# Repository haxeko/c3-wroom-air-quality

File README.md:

# C3-WROOM Air Quality

Thiết bị đo chất lượng không khí dùng **ESP32-C3-WROOM-02**: bụi mịn PM1.0/PM2.5/PM10 (Plantower **PMS5003**), CO2/nhiệt độ/độ ẩm (Sensirion **SCD40**), màn hình **OLED 1.3" SH1106** và 3 LED RGB địa chỉ hóa báo trạng thái.

Repo gồm **phần cứng** (KiCad, file sản xuất JLCPCB) và **firmware** (Matter over Wi-Fi: Apple Home, Google Home, Home Assistant).

## Cấu trúc thư mục

```
.
├── hardware/                 Thiết kế phần cứng
│   ├── kicad/
│   │   ├── main/             Bản chính: 3 LED XL-1615, JLC lắp 2 mặt
│   │   ├── led2020/          Bản thử nghiệm: JLC lắp 1 mặt, tự hàn 3 LED WS2812B-2020
│   │   └── lib/              Thư viện ký hiệu + footprint dùng chung (PM25)
│   ├── production/<bản>/     File đặt JLCPCB: gerber, BOM, CPL
│   ├── docs/<bản>/           Sơ đồ nguyên lý PDF, layout PDF, BOM đầy đủ, tọa độ đầy đủ
│   ├── mechanical/           Đường viền board (DXF) để thiết kế vỏ
│   └── cost/                 Kho giá linh kiện + BOQ giá thành 1 sản phẩm
├── firmware/                 Firmware ESP32-C3: Matter over Wi-Fi (ESP-IDF + esp-matter)
│   ├── main/                 Mã nguồn; chân GPIO đặt trong main/Kconfig.projbuild (menuconfig)
│   └── docs/                 Kịch bản kiểm tra khi ghép nối thất bại
└── docs/                     Tài liệu: gán chân, đặt hàng JLC, hàn LED, sửa lỗi, lịch sử
```

## Thông số board

| Mục | Giá trị |
|---|---|
| Kích thước | 51,4 × 31,4 mm, 2 lớp, dày 1,6 mm, bo góc R1,7 |
| Anten | Khoét 6 × 19 mm ở cạnh phải, không đổ đồng vùng anten |
| Nguồn | USB-C chỉ cấp nguồn (5 V), cổng lồi khỏi mép board 1,2 mm |
| Ổn áp | AMS1117-3.3 cho ESP32 + OLED; AP2112K-3.3 riêng cho SCD40 |
| Nạp firmware | 6 pad tròn J5 (UART0 + IO9), xem [docs/pinout.md](docs/pinout.md) |
| Nút | SW2 TS-1187A nối IO10 (nút người dùng) |

## Các bản phần cứng

| Bản | Thư mục | Khác biệt |
|---|---|---|
| **main** (v25) | `hardware/kicad/main` | 3 LED XL-1615 (1,6 × 1,5 mm) do JLC hàn; linh kiện ở cả 2 mặt |
| **led2020** | `hardware/kicad/led2020` | JLC chỉ lắp mặt dưới; mặt trên tự hàn 3 LED WS2812B-2020; tụ LED và R7 chuyển xuống mặt dưới |

Bản cũ v19 (5 LED, header nạp xuyên lỗ, nút RESET ở EN) không có trong repo; xem [docs/changelog.md](docs/changelog.md).

## Bắt đầu nhanh

- **Mở thiết kế:** KiCad 7 trở lên, mở `hardware/kicad/main/pm25.kicad_pro`.
- **Đặt hàng:** làm theo [docs/assembly-jlcpcb.md](docs/assembly-jlcpcb.md).
- **Build và nạp firmware:** đọc [firmware/README.md](firmware/README.md). Chân GPIO đặt trong `idf.py menuconfig`; kiểm tra lỗi ghép nối theo [firmware/docs/commissioning-test-plan.md](firmware/docs/commissioning-test-plan.md).

## Tài liệu

- [Gán chân GPIO và các giắc](docs/pinout.md)
- [Đặt hàng JLCPCB](docs/assembly-jlcpcb.md)
- [Hướng dẫn hàn LED 2020](docs/led-soldering.md)
- [Sửa lỗi phần cứng](docs/troubleshooting.md)
- [Lịch sử thay đổi](docs/changelog.md)

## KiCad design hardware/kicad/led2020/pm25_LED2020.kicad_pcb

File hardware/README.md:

# Phần cứng

| Thư mục | Nội dung |
|---|---|
| `kicad/main/` | Project KiCad bản chính v25 (`pm25.kicad_pro`) |
| `kicad/led2020/` | Project KiCad bản led2020 (`pm25_LED2020.kicad_pro`) |
| `kicad/lib/` | Thư viện dùng chung: `PM25.kicad_sym` (ký hiệu ESP32-C3-WROOM-02, USB-C 16P, XL-1615) và `PM25.pretty` (footprint USB-C HX 16P, LED XL-1615, nút TS-1187A, pad nạp) |
| `production/<bản>/` | Gerber + drill, BOM, CPL đúng mẫu JLCPCB (xlsx) và bản CSV |
| `docs/<bản>/` | Sơ đồ nguyên lý PDF, layout PDF, BOM đầy đủ (kèm linh kiện tự hàn, không gồm module ESP), tọa độ đầy đủ |
| `mechanical/` | Đường viền board DXF để vẽ vỏ |
| `cost/` | Kho giá linh kiện và BOQ giá thành 1 sản phẩm |

Mở bằng **KiCad 7 trở lên**. Bảng thư viện (`fp-lib-table`, `sym-lib-table`) trong mỗi project trỏ tới `../lib`, nên giữ nguyên cấu trúc thư mục khi sao chép.

Quy tắc thiết kế: đường tín hiệu 0,15–0,2 mm, nguồn 0,3–0,5 mm; via 0,6/0,3 mm; khoảng cách 0,2 mm; đồng cách mép board 0,3 mm; GND đổ hai mặt có via khâu.

Khi sửa board: xuất lại Gerber/BOM/CPL vào `production/<bản>/`, PDF vào `docs/<bản>/`, ghi thay đổi vào `docs/changelog.md` ở thư mục gốc. Nhớ giữ hiệu chỉnh góc CPL (J1 +180°, U6 +90°) – xem `docs/assembly-jlcpcb.md`.

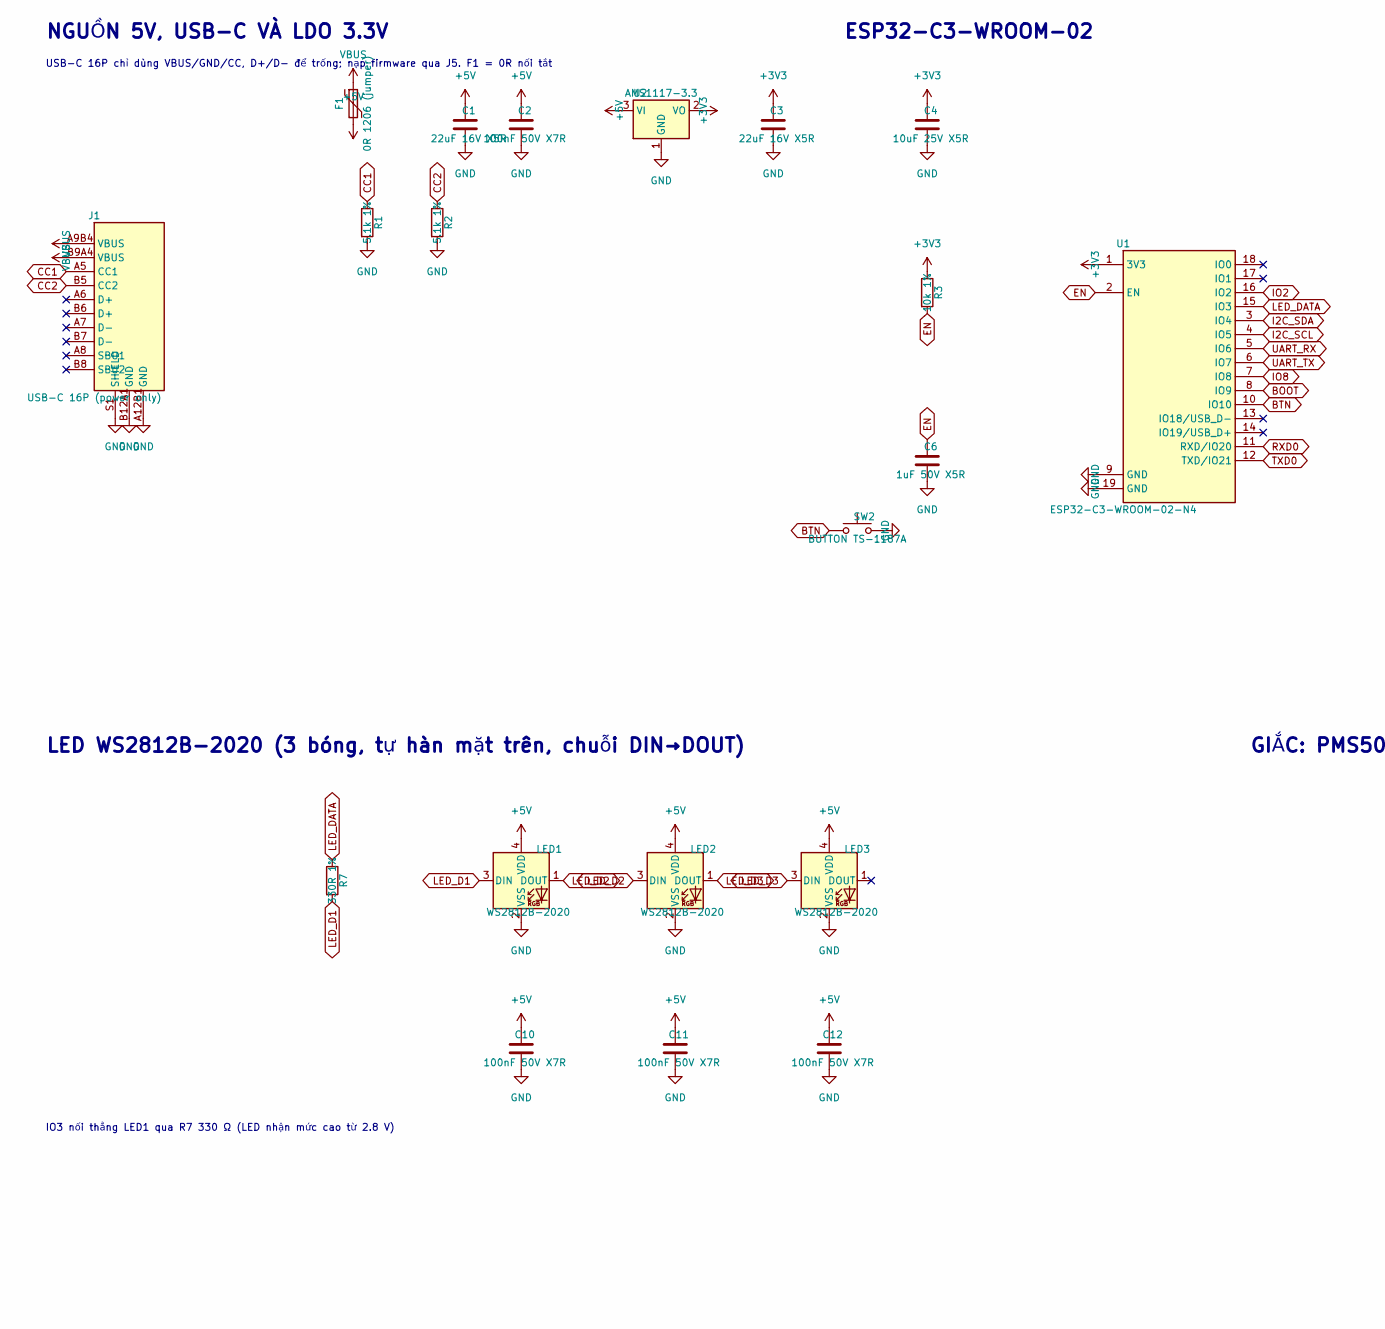
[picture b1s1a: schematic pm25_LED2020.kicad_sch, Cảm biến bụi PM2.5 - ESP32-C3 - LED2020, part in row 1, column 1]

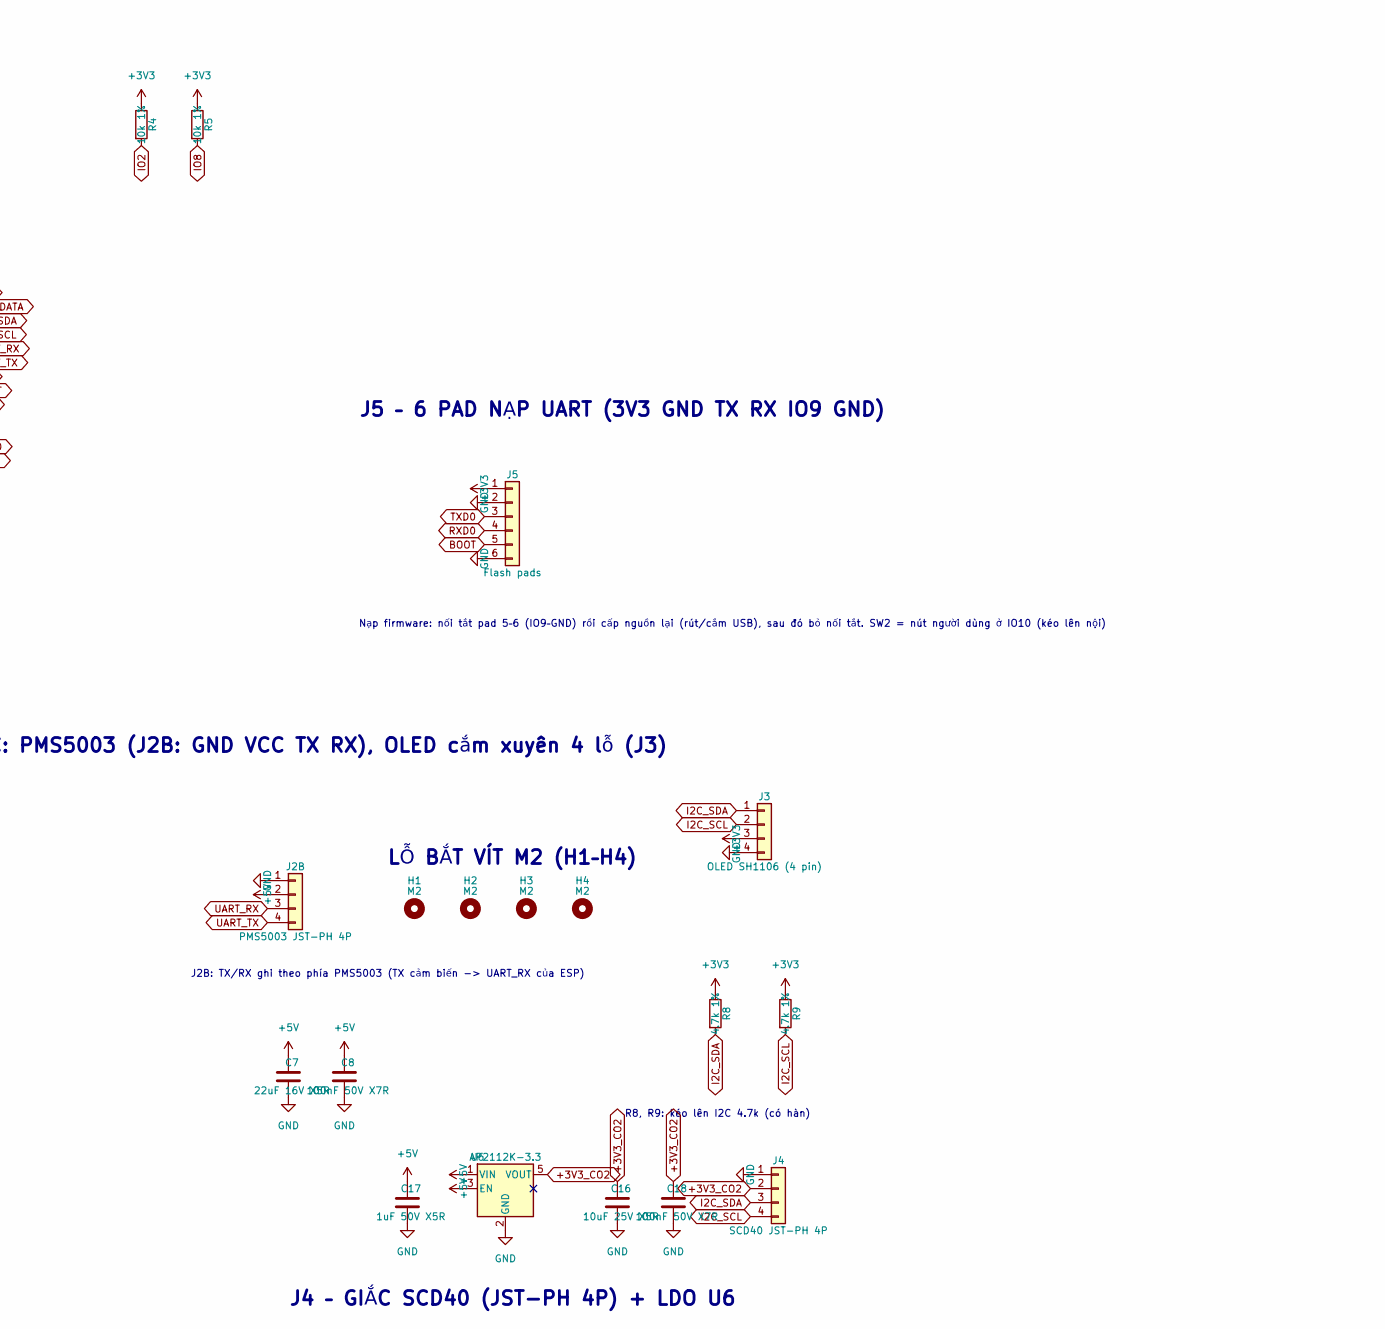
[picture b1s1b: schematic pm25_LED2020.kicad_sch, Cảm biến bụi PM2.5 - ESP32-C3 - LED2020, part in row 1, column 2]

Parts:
C1, C3, C7: 22uF 16V X5R; C_0805_2012Metric
C2, C8, C10, C11, C12, C18: 100nF 50V X7R; C_0603_1608Metric
C4, C16: 10uF 25V X5R; C_0805_2012Metric
C6, C17: 1uF 50V X5R; C_0603_1608Metric
F1: 0R 1206 (jumper); Fuse_1206_3216Metric
H1, H2, H3, H4: M2; MountingHole_2.2mm_M2
J1: USB-C 16P (power only); USB_C_HX_TYPE-C-16PIN
J2B: PMS5003 JST-PH 4P; JST_PH_B4B-PH-K_1x04_P2.00mm_Vertical
J3: OLED SH1106 (4 pin); PinHeader_1x04_P2.54mm_Vertical
J4: SCD40 JST-PH 4P; JST_PH_B4B-PH-K_1x04_P2.00mm_Vertical
J5: Flash pads; Flash_Pads_1x06_P2.54mm
LED1, LED2, LED3: WS2812B-2020; LED_WS2812B-2020_PLCC4_2.0x2.0mm
R1, R2: 5.1k 1%; R_0603_1608Metric
R3, R4, R5: 10k 1%; R_0603_1608Metric
R7: 330R 1%; R_0603_1608Metric
R8, R9: 4.7k 1%; R_0603_1608Metric
SW2: BUTTON TS-1187A; SW_Push_1P1T_XKB_TS-1187A
U1: ESP32-C3-WROOM-02-N4; ESP32-C3-WROOM-02
U2: AMS1117-3.3; SOT-223-3_TabPin2
U6: AP2112K-3.3; SOT-23-5

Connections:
+3V3: C3.1, C4.1, J3.3, J5.1, R3.1, R4.1, R5.1, R8.1, R9.1, U1.1 (3V3), U2.2 (VO)
+3V3_CO2: C16.1, C18.1, J4.2, U6.5 (VOUT)
+5V: C1.1, C2.1, C7.1, C8.1, C10.1, C11.1, C12.1, C17.1, F1.2, J2B.2, LED1.4 (VDD), LED2.4 (VDD), LED3.4 (VDD), U2.3 (VI), U6.1 (VIN), U6.3 (EN)
BOOT: J5.5, U1.8 (IO9)
BTN: SW2.1, U1.10 (IO10)
CC1: J1.A5 (CC1), R1.1
CC2: J1.B5 (CC2), R2.1
EN: C6.1, R3.2, U1.2 (EN)
GND: C1.2, C2.2, C3.2, C4.2, C6.2, C7.2, C8.2, C10.2, C11.2, C12.2, C16.2, C17.2, C18.2, J1.A12B1 (GND), J1.B12A1 (GND), J1.S1 (SHIELD), J2B.1, J3.4, J4.1, J5.2, J5.6, LED1.2 (VSS), LED2.2 (VSS), LED3.2 (VSS), R1.2, R2.2, SW2.2, U1.9 (GND), U1.19 (GND), U2.1 (GND), U6.2 (GND)
I2C_SCL: J3.2, J4.4, R9.2, U1.4 (IO5)
I2C_SDA: J3.1, J4.3, R8.2, U1.3 (IO4)
IO2: R4.2, U1.16 (IO2)
IO8: R5.2, U1.7 (IO8)
LED_D1: LED1.3 (DIN), R7.2
LED_D2: LED1.1 (DOUT), LED2.3 (DIN)
LED_D3: LED2.1 (DOUT), LED3.3 (DIN)
LED_DATA: R7.1, U1.15 (IO3)
RXD0: J5.4, U1.11 (RXD/IO20)
TXD0: J5.3, U1.12 (TXD/IO21)
UART_RX: J2B.3, U1.5 (IO6)
UART_TX: J2B.4, U1.6 (IO7)
VBUS: F1.1, J1.A9B4 (VBUS), J1.B9A4 (VBUS)

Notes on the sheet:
NGUỒN 5V, USB-C VÀ LDO 3.3V
USB-C 16P chỉ dùng VBUS/GND/CC, D+/D- để trống; nạp firmware qua J5. F1 = 0R nối tắt
ESP32-C3-WROOM-02
J5 – 6 PAD NẠP UART (3V3 GND TX RX IO9 GND)
Nạp firmware: nối tắt pad 5–6 (IO9–GND) rồi cấp nguồn lại (rút/cắm USB), sau đó bỏ nối tắt. SW2 = nút người dùng ở IO10 (kéo lên nội)
LED WS2812B-2020 (3 bóng, tự hàn mặt trên, chuỗi DIN→DOUT)
GIẮC: PMS5003 (J2B: GND VCC TX RX), OLED cắm xuyên 4 lỗ (J3)
R8, R9: kéo lên I2C 4.7k (có hàn)
J4 – GIẮC SCD40 (JST-PH 4P) + LDO U6
LỖ BẮT VÍT M2 (H1–H4)
J2B: TX/RX ghi theo phía PMS5003 (TX cảm biến -> UART_RX của ESP)
IO3 nối thẳng LED1 qua R7 330 Ω (LED nhận mức cao từ 2.8 V)

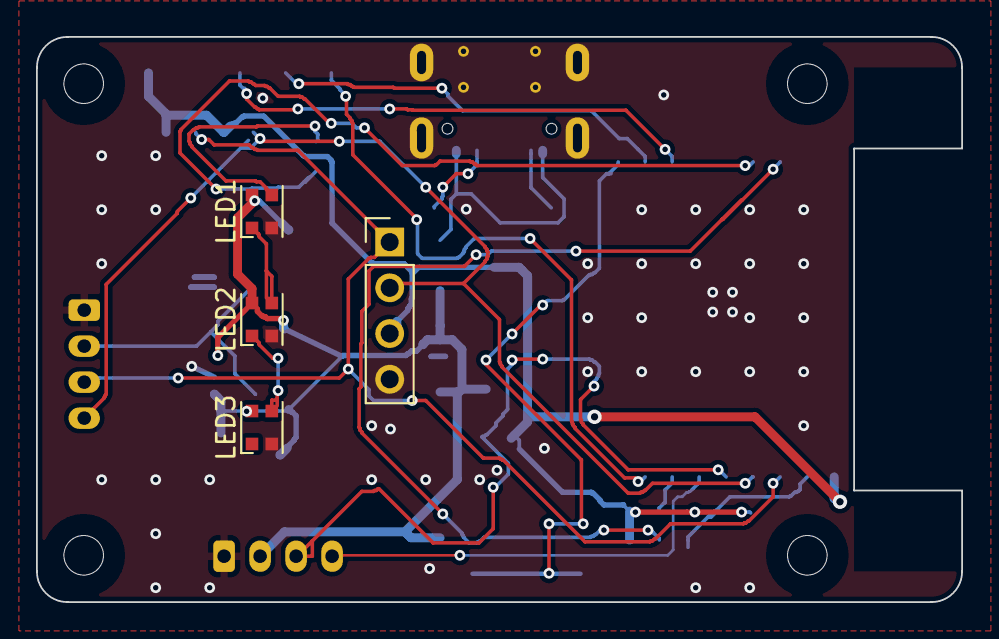
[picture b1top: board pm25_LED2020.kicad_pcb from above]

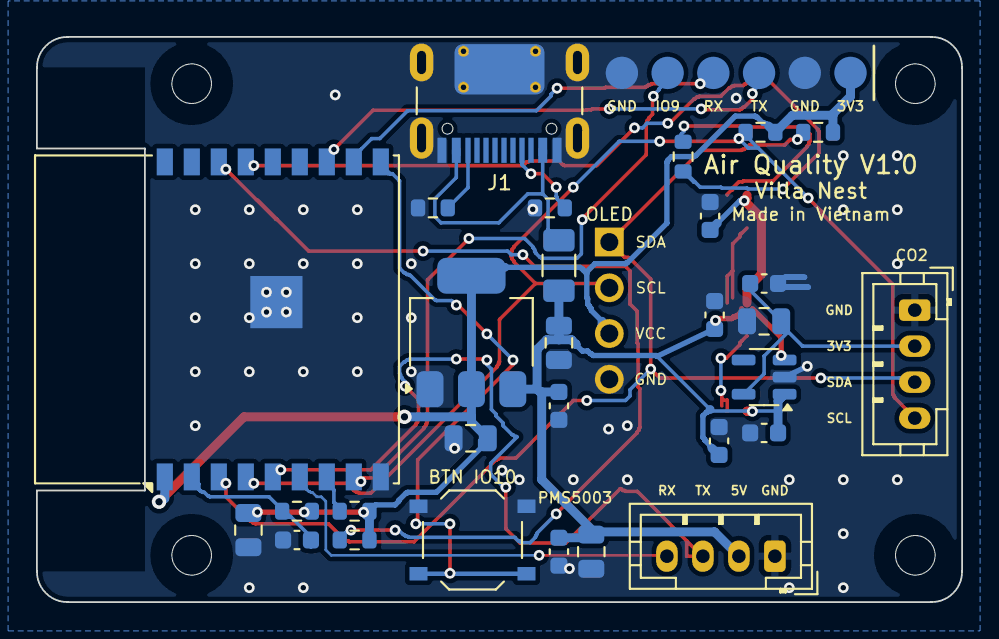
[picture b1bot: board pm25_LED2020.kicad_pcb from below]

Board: 2 copper layers, 51.4 x 31.4 mm, 38 parts (30 on the bottom side), 22 nets.
